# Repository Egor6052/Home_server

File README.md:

Home Server Project
---
This home server is designed for remote access, monitoring, and management. The core hardware setup consists of a Raspberry Pi 5, an STM32F401RCT6 microcontroller, a 5-port network switch, a Hikvision camera with a 12V power connector, and a 400W power supply.

---

### Paspberry Module:
- Camera streaming RTSP to https;
- Systemd services;
- UART to STM32 conect;
- Dashboard for controlling the server;

### STM32 Module:
- Controller;
- WATCHDOG system can reboot Raspberry Pi if it doesn't have a response from it;
- Physical reboot button;
- Temperature inside the server;
- Cooler controlling;
- Connect to the street controller to get the humidity and temperature data;

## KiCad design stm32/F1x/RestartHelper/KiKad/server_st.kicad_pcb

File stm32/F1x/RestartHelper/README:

# UART transmit source code for stm32f103c8t6

## Problem
During server operation a memory overflow occurs, causing the device to hang and become unresponsive. A helper device based on STM32 polls the server every 20 minutes; if no response is received, it triggers a pin to reboot the server. The OLED shows temperature, humidity, and the time of the last successful server response.

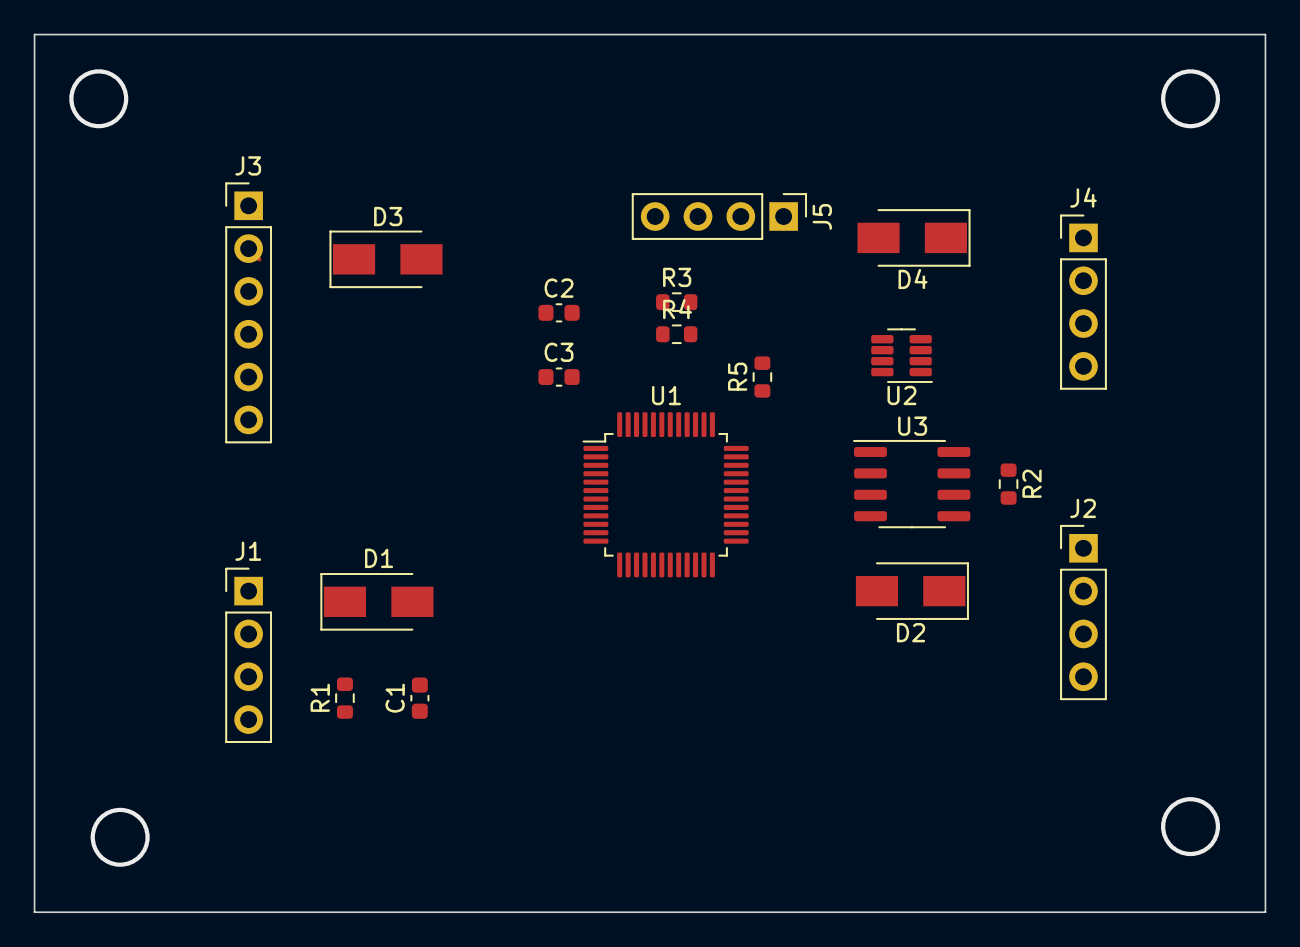
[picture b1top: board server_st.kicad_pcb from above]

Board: 2 copper layers, 73.0 x 52.1 mm, 20 parts (0 on the bottom side), 23 nets.

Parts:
C1: 0.1uF; C_0603_1608Metric
C2, C3: 20pF; C_0603_1608Metric
D1, D2, D3, D4: UF4007; D_SMA
J1: Conn_01x04_Female_Temperature; PinHeader_1x04_P2.54mm_Vertical
J2: Conn_01x04_Female_Button; PinHeader_1x04_P2.54mm_Vertical
J3: Conn_01x06_Female_Relay; PinHeader_1x06_P2.54mm_Vertical
J4: Conn_01x04_Female; PinHeader_1x04_P2.54mm_Vertical
J5: Conn_01x04_Female_SWD; PinHeader_1x04_P2.54mm_Vertical
R1, R3, R4: 4.7k; R_0603_1608Metric
R2: 1k; R_0603_1608Metric
R5: 10k; R_0603_1608Metric
U1: STM32F103C8Tx; LQFP-48_7x7mm_P0.5mm
U2: INA219AxDCN; SOT-23-8
U3: MAX485E; SOIC-8_3.9x4.9mm_P1.27mm

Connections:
+3V3: C1.1, J1.2, J5.1, R1.1, R3.1, R4.1, U1.1 (VBAT), U1.9 (VDDA), U1.24 (VDD), U1.36 (VDD), U1.48 (VDD)
+5V: J2.2, J3.1, J4.2, U2.4 (VS), U3.8 (VCC)
Earth: C1.2, C2.2, C3.2, D1.2 (A), D2.2 (A), D3.2 (A), D4.2 (A), J5.4, R5.2, U1.5 (PD0), U1.6 (PD1), U1.8 (VSSA), U1.23 (VSS), U1.35 (VSS), U1.47 (VSS), U2.3 (GND), U3.5 (GND)
unnamed: D1.1 (K), J1.1
unnamed: D2.1 (K), J2.1
unnamed: D3.1 (K), J3.2
unnamed: D4.1 (K), J4.1
unnamed: J1.4, R1.2, U1.16 (PA6)
unnamed: J2.4, U1.25 (PB12)
unnamed: J3.3, U1.10 (PA0)
unnamed: J3.4, U1.11 (PA1)
unnamed: J3.5, U1.12 (PA2)
unnamed: J3.6, U1.13 (PA3)
unnamed: J4.3, R2.1, U3.7 (B)
unnamed: J4.4, R2.2, U3.6 (A)
unnamed: R3.2, U1.42 (PB6), U2.5 (SCL)
unnamed: R4.2, U1.43 (PB7), U2.6 (SDA)
unnamed: R5.1, U1.44 (BOOT0)
unnamed: U1.21 (PB10), U3.4 (DI)
unnamed: U1.22 (PB11), U3.1 (RO)
unnamed: U1.29 (PA8), U3.2 (~RE), U3.3 (DE)
unnamed: J5.2, U1.34 (PA13)
unnamed: J5.3, U1.37 (PA14)

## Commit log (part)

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2025-11-25 Semrver runs on a Raspberry and collects data from stm32f103c8t6
2025-12-06 Add server home page source code
2026-03-14 New update for Asus TinkerBoard S
2026-03-14 Fix timestump function
2026-05-04 New night update
2026-05-04 Update with Nginx. Night Update
2026-05-05 add nginx conf. Update daemon module.
2026-06-07 Add stm32 board for emergency reboot and server system availability check
2026-06-07 Stable Night update.
2026-06-15 rename main folder
2026-06-15 Add audio streamer. Change UART functions.
2026-06-15 Fixed uart logic
2026-06-29 Add curl and nginx scripts
